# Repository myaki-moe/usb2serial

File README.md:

# usb2serial

A low cost open source USB to 3 port serial (2*UART + 1*DBUS) adapter.

Based on STM32F103 (blue pill) and bluepill-serial-monster firmware, usb2serial supports USB CDC protocol for plug and play (PnP).

低成本开源USB到三路串口 (2*UART + 1*DBUS) 转换器. 

基于STM32F103 (blue pill) bluepill-serial-monster固件, usb2serial支持基于USB CDC协议的即插即用.

## Quick Start | 快速开始

1. PCB proofing using GERBER file `usb2serial_pcb/gerber/`
2. SMD or hand soldering using [ibom](usb2serial_pcb/bom/ibom.html)
3. Build bluepill-serial-monster firmware
4. Pull-up BOOT0 and reset MCU to enter bootloader.
5. Flash the firmware using [stm32flash](https://sourceforge.net/p/stm32flash) from UART1
6. Testing

```bash
# connect TX and RX first
# list all serial device
ls /dev/ttyACM*
# do a loopback test
minicom -D /dev/ttyACM{YOUR_DEVICE_NUMBER}
```

1. 使用GERBER文件 `usb2serial_pcb/gerber/` 打样PCB
2. SMT或使用 [ibom](usb2serial_pcb/bom/ibom.html)手工焊接
3. 编译bluepill-serial-monster固件
4. 拉高BOOT0进入烧录模式
5. 使用 [stm32flash](https://sourceforge.net/p/stm32flash) 从UART1烧录固件
6. 测试

```bash
# connect TX and RX first
# list all serial device
ls /dev/ttyACM*
# do a loopback test
minicom -D /dev/ttyACM{YOUR_DEVICE_NUMBER}
```

## Toolchains | 工具链

* PCB Design: KiCad 6.0.9
* Complier: arm-none-eabi-gcc 12.2.0
* Firmware Programmer: [stm32flash](https://sourceforge.net/p/stm32flash) 0.7

* PCB设计: KiCad 6.0.9
* 编译器: arm-none-eabi-gcc 12.2.0
* 固件烧录: [stm32flash](https://sourceforge.net/p/stm32flash) 0.7

## License | 许可证

* The USB2CAN project is released under GPLv3 license.

* The bluepill-serial-monster project is released under MIT license.

* USB2CAN项目基于GPLv3协议发布

* bluepill-serial-monster项目基于MIT协议分发

## Related Projects | 相关项目

[bluepill-serial-monster](https://github.com/r2axz/bluepill-serial-monster)

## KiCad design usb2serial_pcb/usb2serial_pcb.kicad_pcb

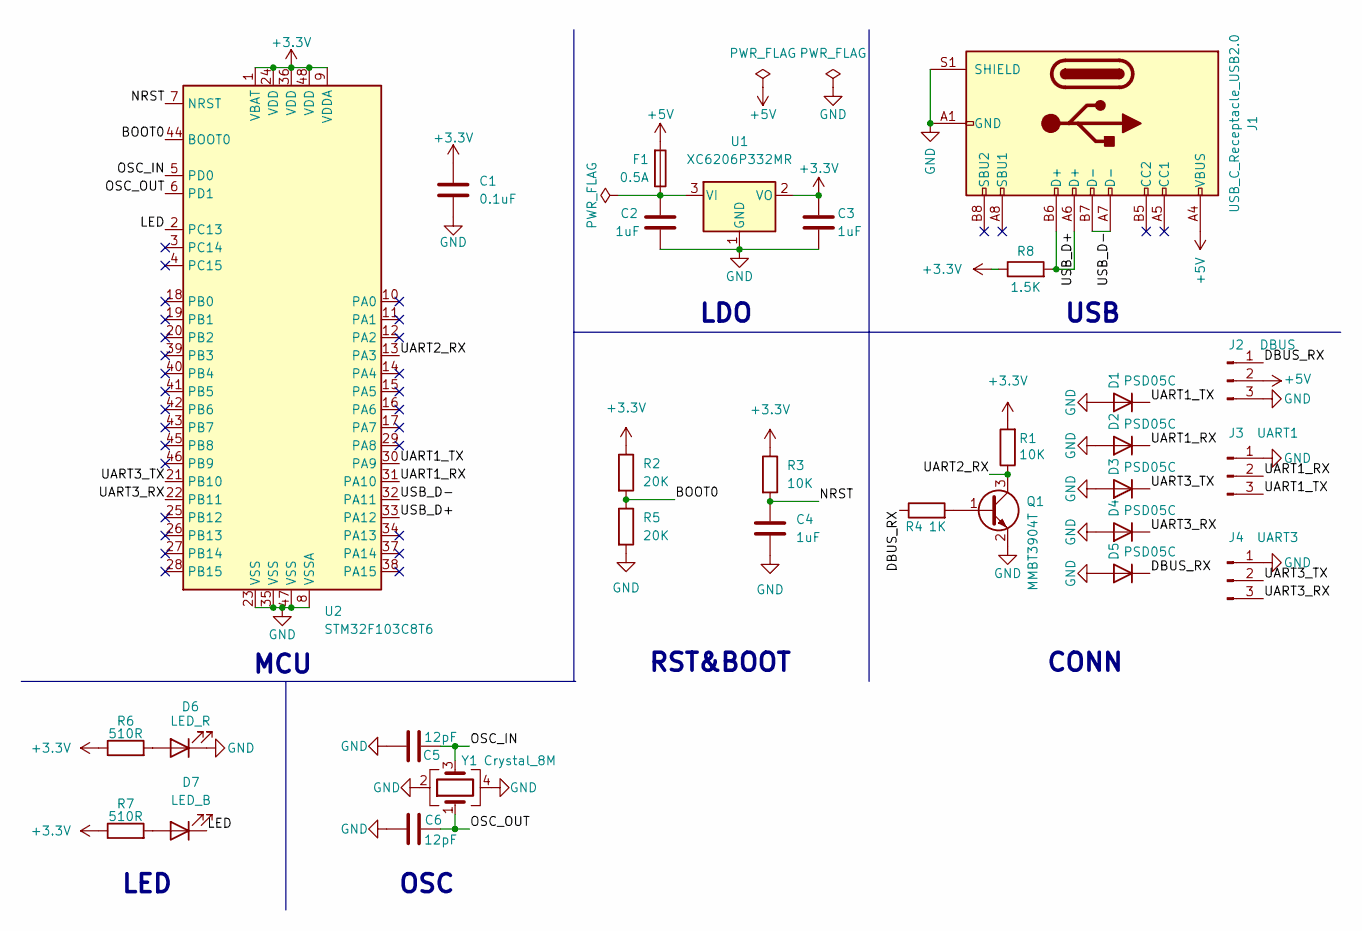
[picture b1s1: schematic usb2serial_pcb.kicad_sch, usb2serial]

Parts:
C1: 0.1uF; C_0402_1005Metric
C2, C3, C4: 1uF; C_0402_1005Metric
C5, C6: 12pF; C_0402_1005Metric
D1, D2, D3, D4, D5: PSD05C; D_SOD-323
D6: LED_R; D_0402_1005Metric
D7: LED_B; D_0402_1005Metric
F1: 0.5A; Fuse_0603_1608Metric
J1: USB_C_Receptacle_USB2.0; USB_C_Receptacle_Palconn_UTC16-G
J2: DBUS; PinHeader_1x03_P2.54mm_Horizontal
J3: UART1; JST_GH_SM03B-GHS-TB_1x03-1MP_P1.25mm_Horizontal
J4: UART3; JST_GH_SM03B-GHS-TB_1x03-1MP_P1.25mm_Horizontal
Q1: MMBT3904T; SOT-523
R1, R3: 10K; R_0402_1005Metric
R2, R5: 20K; R_0402_1005Metric
R4: 1K; R_0402_1005Metric
R6, R7: 510R; R_0402_1005Metric
R8: 1.5K; R_0402_1005Metric
U1: XC6206P332MR; SOT-23
U2: STM32F103C8T6; LQFP-48_7x7mm_P0.5mm
Y1: Crystal_8M; Crystal_SMD_3225-4Pin_3.2x2.5mm

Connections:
+3.3V: C1.1, C3.1, R1.2, R2.1, R3.1, R6.1, R7.1, R8.1, U1.2 (VO), U2.1 (VBAT), U2.9 (VDDA), U2.24 (VDD), U2.36 (VDD), U2.48 (VDD)
+5V: F1.2, J1.A4 (VBUS), J1.A9 (VBUS), J1.B4 (VBUS), J1.B9 (VBUS), J2.2
/BOOT0: R2.2, R5.1, U2.44 (BOOT0)
/DBUS_RX: D5.1 (K), J2.1, R4.1
/LED: D7.1 (K), U2.2 (PC13)
/NRST: C4.1, R3.2, U2.7 (NRST)
/OSC_IN: C5.2, U2.5 (PD0), Y1.3
/OSC_OUT: C6.2, U2.6 (PD1), Y1.1
/UART1_RX: D2.1 (K), J3.2, U2.31 (PA10)
/UART1_TX: D1.1 (K), J3.3, U2.30 (PA9)
/UART2_RX: Q1.3 (C), R1.1, U2.13 (PA3)
/UART3_RX: D4.1 (K), J4.3, U2.22 (PB11)
/UART3_TX: D3.1 (K), J4.2, U2.21 (PB10)
/USB_D+: J1.A6 (D+), J1.B6 (D+), R8.2, U2.33 (PA12)
/USB_D-: J1.A7 (D-), J1.B7 (D-), U2.32 (PA11)
GND: C1.2, C2.1, C3.2, C4.2, C5.1, C6.1, D1.2 (A), D2.2 (A), D3.2 (A), D4.2 (A), D5.2 (A), D6.1 (K), J1.A1 (GND), J1.A12 (GND), J1.B1 (GND), J1.B12 (GND), J1.S1 (SHIELD), J2.3, J3.1, J4.1, Q1.2 (E), R5.2, U1.1 (GND), U2.8 (VSSA), U2.23 (VSS), U2.35 (VSS), U2.47 (VSS), Y1.2, Y1.4
unnamed: C2.2, F1.1, U1.3 (VI)
unnamed: D6.2 (A), R6.2
unnamed: D7.2 (A), R7.2
unnamed: Q1.1 (B), R4.2

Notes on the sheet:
LED
CONN
RST&BOOT
USB
OSC
LDO
MCU

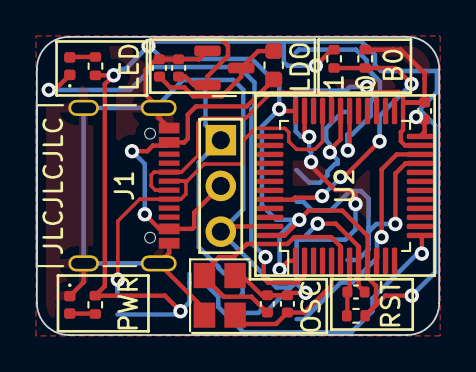
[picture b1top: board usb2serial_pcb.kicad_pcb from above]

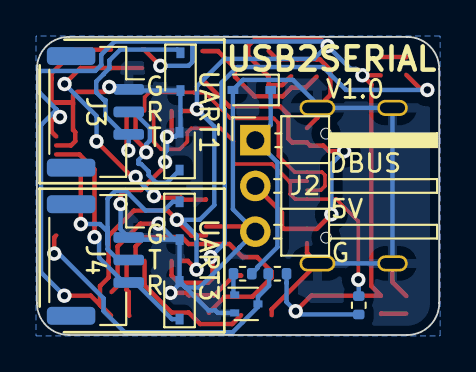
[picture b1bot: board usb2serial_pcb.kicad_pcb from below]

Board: 2 copper layers, 22.4 x 16.6 mm, 30 parts (12 on the bottom side), 20 nets.

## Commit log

2022-11-12 add bluepill-serial-monster firmware
2022-11-12 add GPLv3 license and .gitattributes
2022-11-14 add pcb design V1.0
2022-11-14 add gerber and ibom
2022-11-14 fix path naming issue in .gitattributes
2022-11-29 add pull up register for USB enum
2023-01-23 doc: update doc
